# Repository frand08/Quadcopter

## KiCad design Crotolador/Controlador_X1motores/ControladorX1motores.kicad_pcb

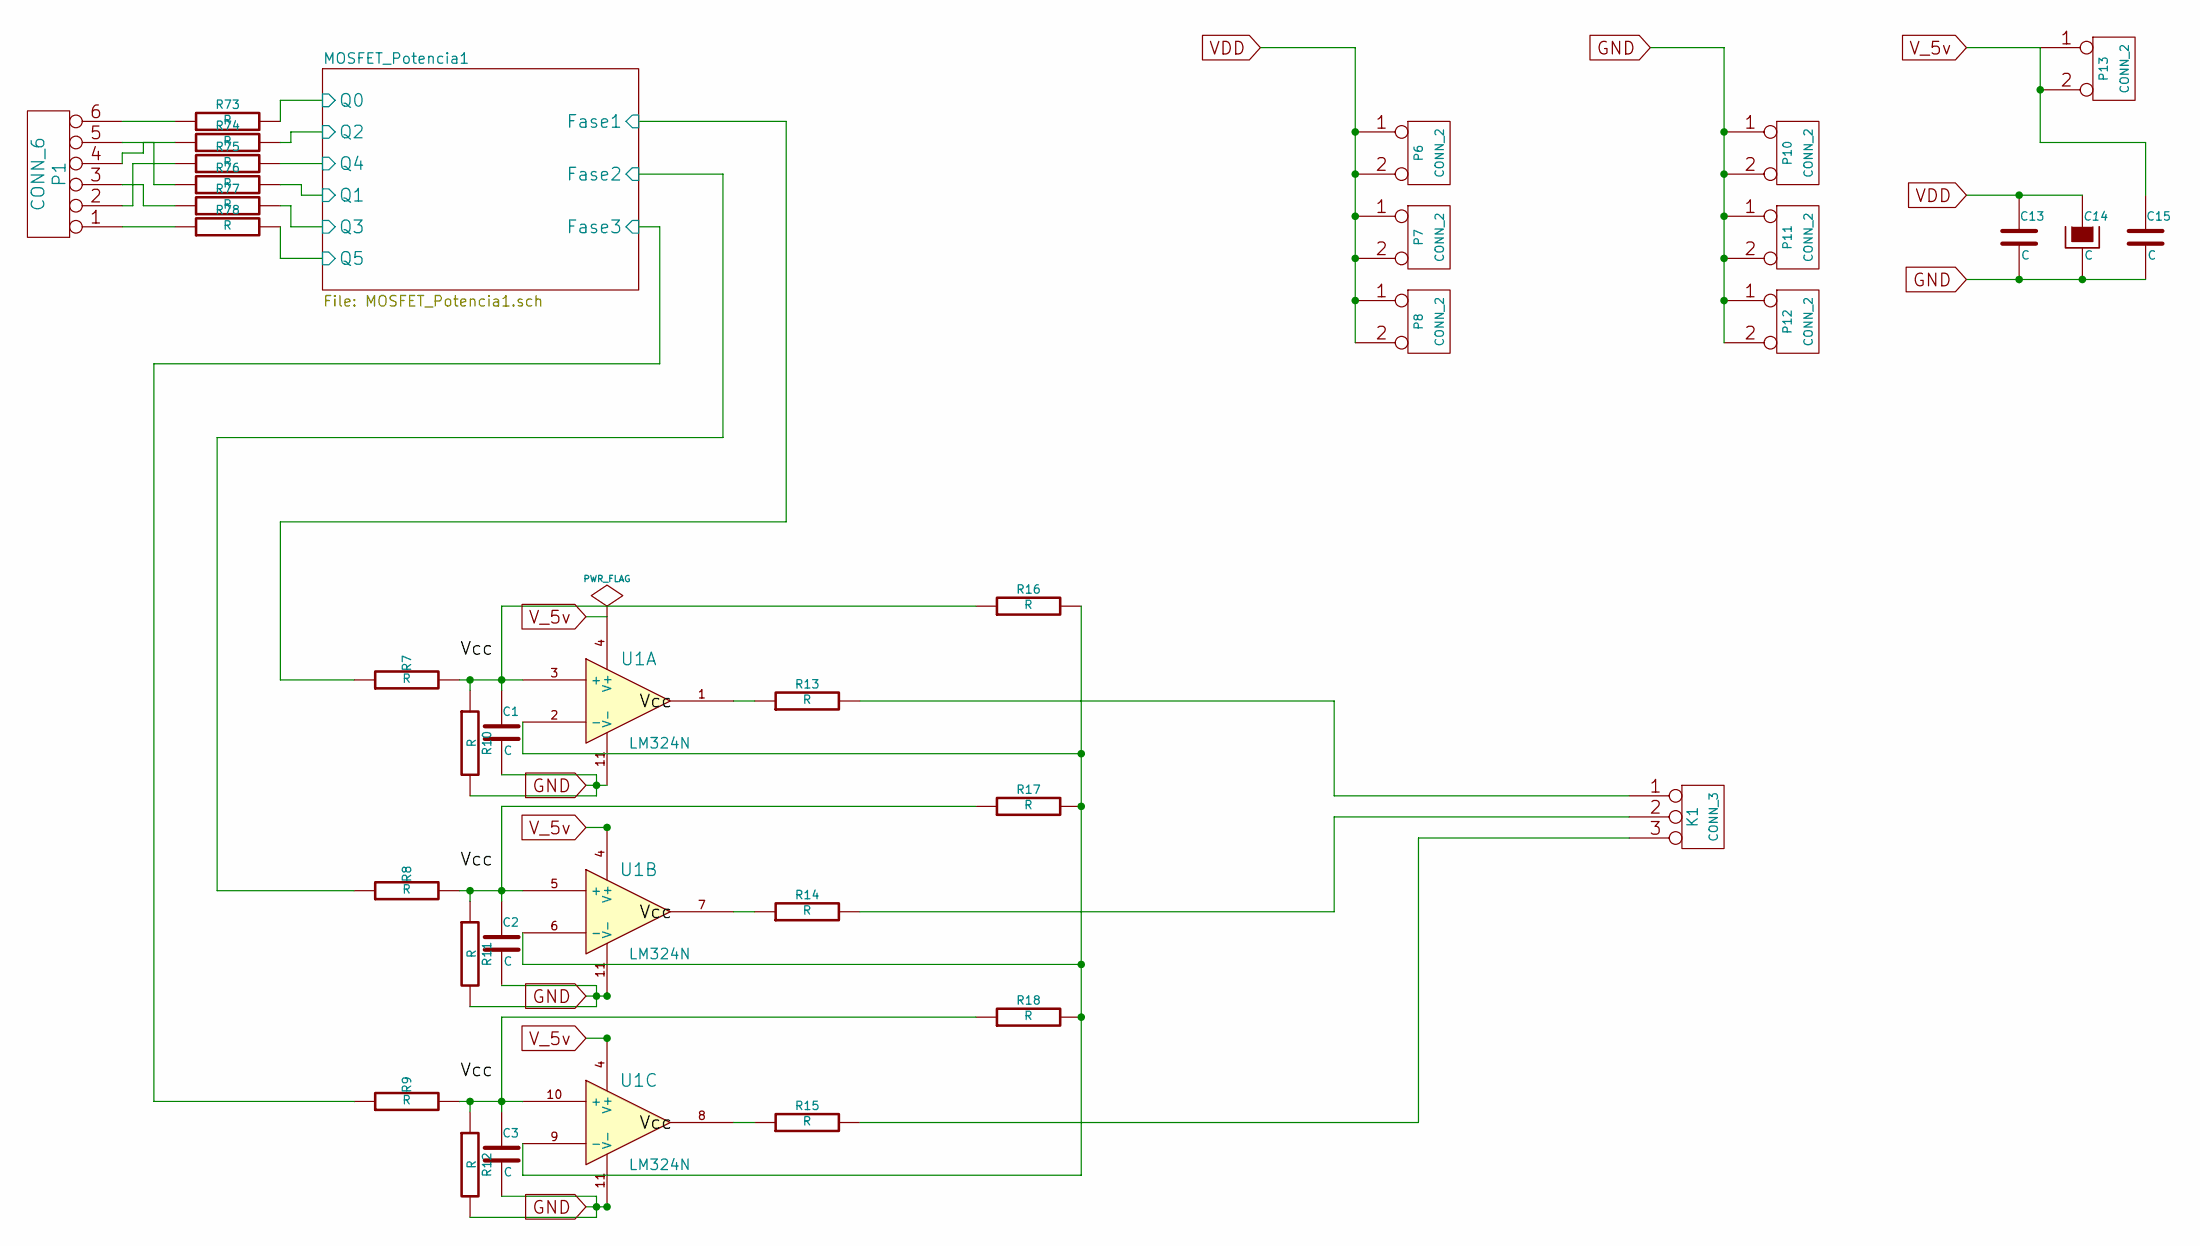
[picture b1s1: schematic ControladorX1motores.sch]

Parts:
C1, C2, C3, C13, C14, C15: C
K1: CONN_3
P1: CONN_6
P6, P7, P8, P10, P11, P12, P13: CONN_2
R7, R8, R9, R10, R11, R12, R13, R14, R15, R16, R17, R18, R73, R74, R75, R76, R77, R78: R
U1: LM324N

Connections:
/MOSFET_Potencia1/Fase1: R7.1; also elsewhere on the board
/MOSFET_Potencia1/Fase2: R8.1; also elsewhere on the board
/MOSFET_Potencia1/Fase3: R9.1; also elsewhere on the board
/MOSFET_Potencia1/Q0: R73.2; also elsewhere on the board
/MOSFET_Potencia1/Q1: R76.2; also elsewhere on the board
/MOSFET_Potencia1/Q2: R74.2; also elsewhere on the board
/MOSFET_Potencia1/Q3: R77.2; also elsewhere on the board
/MOSFET_Potencia1/Q4: R75.2; also elsewhere on the board
/MOSFET_Potencia1/Q5: R78.2; also elsewhere on the board
GND: C1.2, C2.2, C3.2, C13.2, C14.2, C15.2, P10.1, P10.2 (PM), P11.1, P11.2 (PM), P12.1, P12.2 (PM), R10.2, R11.2, R12.2, U1.11 (V-); also elsewhere on the board
unnamed: C1.1, R7.2, R10.1, R16.1, U1.3 (+)
unnamed: R13.1, U1.1
unnamed: C2.1, R8.2, R11.1, R17.1, U1.5 (+)
unnamed: R14.1, U1.7
unnamed: C3.1, R9.2, R12.1, R18.1, U1.10 (+)
unnamed: R15.1, U1.8
unnamed: P1.6, R73.1
unnamed: P1.1, R78.1
unnamed: P1.2, R75.1
unnamed: P1.3, R77.1
unnamed: P1.4, R74.1
unnamed: P1.5, R76.1
unnamed: K1.1, R13.2
unnamed: K1.2 (PM), R14.2
unnamed: K1.3, R15.2
unnamed: R16.2, R17.2, R18.2, U1.2 (-), U1.6 (-), U1.9 (-)
VDD: C13.1, C14.1, P6.1, P6.2 (PM), P7.1, P7.2 (PM), P8.1, P8.2 (PM); also elsewhere on the board
V_5v: C15.1, P13.1, P13.2 (PM), U1.4 (V+)

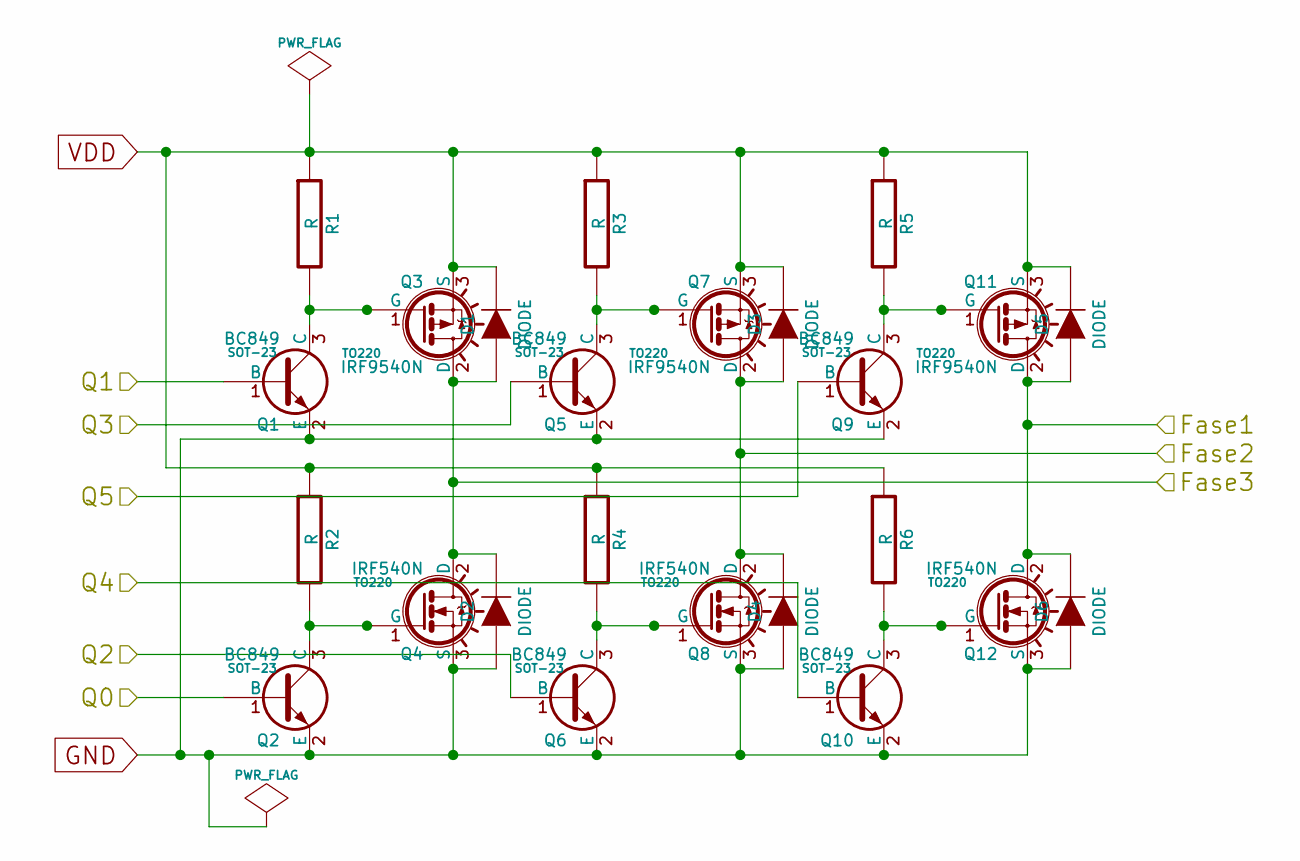
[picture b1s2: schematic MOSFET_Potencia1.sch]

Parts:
D1, D2, D3, D4, D5, D6: DIODE
Q1, Q2, Q5, Q6, Q9, Q10: BC849; SOT-23
Q3, Q7, Q11: IRF9540N; TO220
Q4, Q8, Q12: IRF540N; TO220
R1, R2, R3, R4, R5, R6: R

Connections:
/MOSFET_Potencia1/Fase1: D5.1 (A), D6.2 (K), Q11.2 (D), Q12.2 (D); also elsewhere on the board
/MOSFET_Potencia1/Fase2: D3.1 (A), D4.2 (K), Q7.2 (D), Q8.2 (D); also elsewhere on the board
/MOSFET_Potencia1/Fase3: D1.1 (A), D2.2 (K), Q3.2 (D), Q4.2 (D); also elsewhere on the board
/MOSFET_Potencia1/Q0: Q2.1 (B); also elsewhere on the board
/MOSFET_Potencia1/Q1: Q1.1 (B); also elsewhere on the board
/MOSFET_Potencia1/Q2: Q6.1 (B); also elsewhere on the board
/MOSFET_Potencia1/Q3: Q5.1 (B); also elsewhere on the board
/MOSFET_Potencia1/Q4: Q10.1 (B); also elsewhere on the board
/MOSFET_Potencia1/Q5: Q9.1 (B); also elsewhere on the board
GND: D2.1 (A), D4.1 (A), D6.1 (A), Q1.2 (E), Q2.2 (E), Q4.3 (S), Q5.2 (E), Q6.2 (E), Q8.3 (S), Q9.2 (E), Q10.2 (E), Q12.3 (S); also elsewhere on the board
unnamed: Q9.3 (C), Q11.1 (G), R5.2
unnamed: Q5.3 (C), Q7.1 (G), R3.2
unnamed: Q1.3 (C), Q3.1 (G), R1.2
unnamed: Q2.3 (C), Q4.1 (G), R2.2
unnamed: Q10.3 (C), Q12.1 (G), R6.2
unnamed: Q6.3 (C), Q8.1 (G), R4.2
VDD: D1.2 (K), D3.2 (K), D5.2 (K), Q3.3 (S), Q7.3 (S), Q11.3 (S), R1.1, R2.1, R3.1, R4.1, R5.1, R6.1; also elsewhere on the board

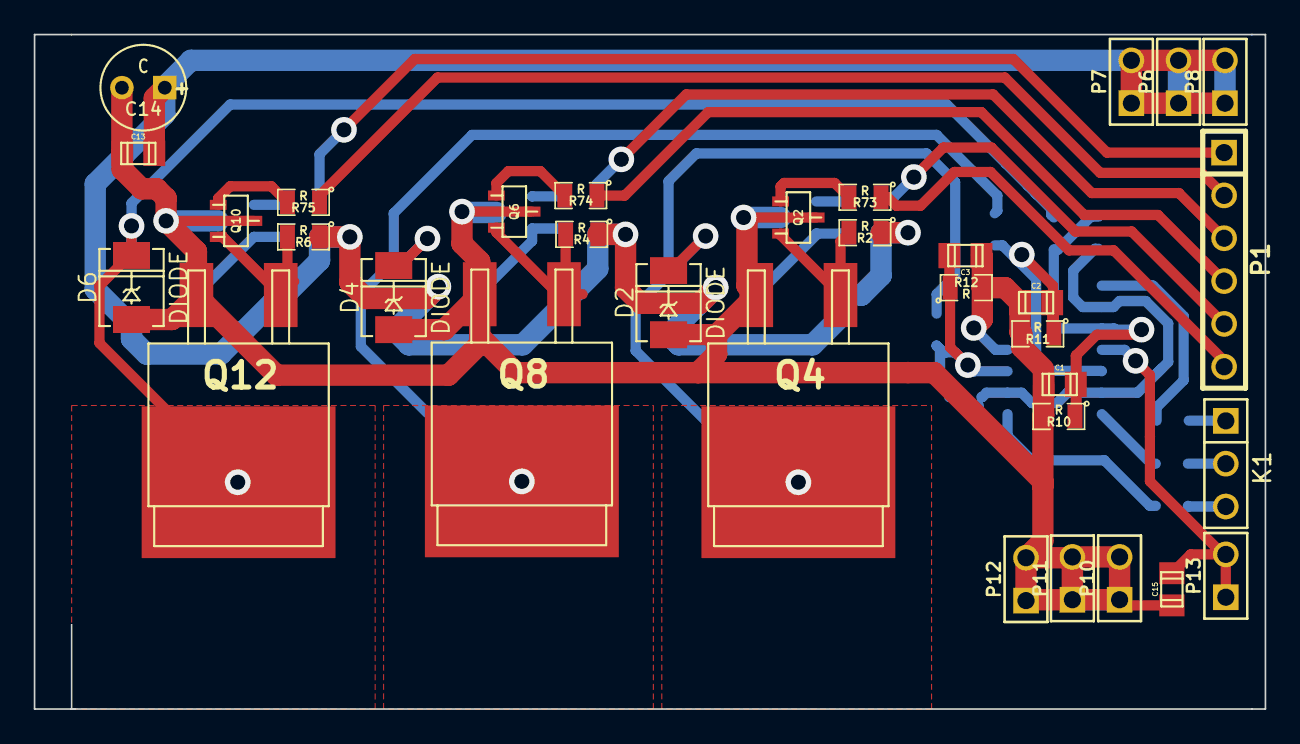
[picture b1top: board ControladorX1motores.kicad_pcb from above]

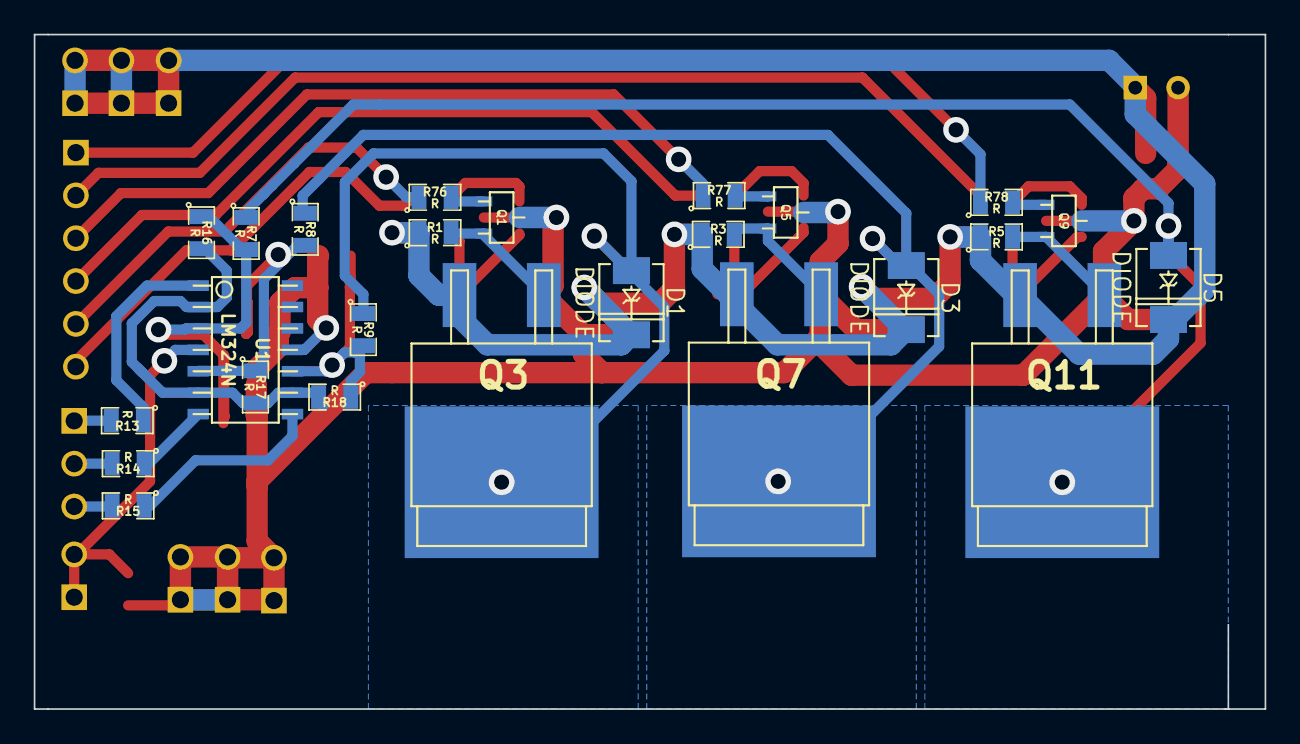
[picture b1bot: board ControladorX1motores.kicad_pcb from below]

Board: 2 copper layers, 73.0 x 40.0 mm, 58 parts (25 on the bottom side), 34 nets.

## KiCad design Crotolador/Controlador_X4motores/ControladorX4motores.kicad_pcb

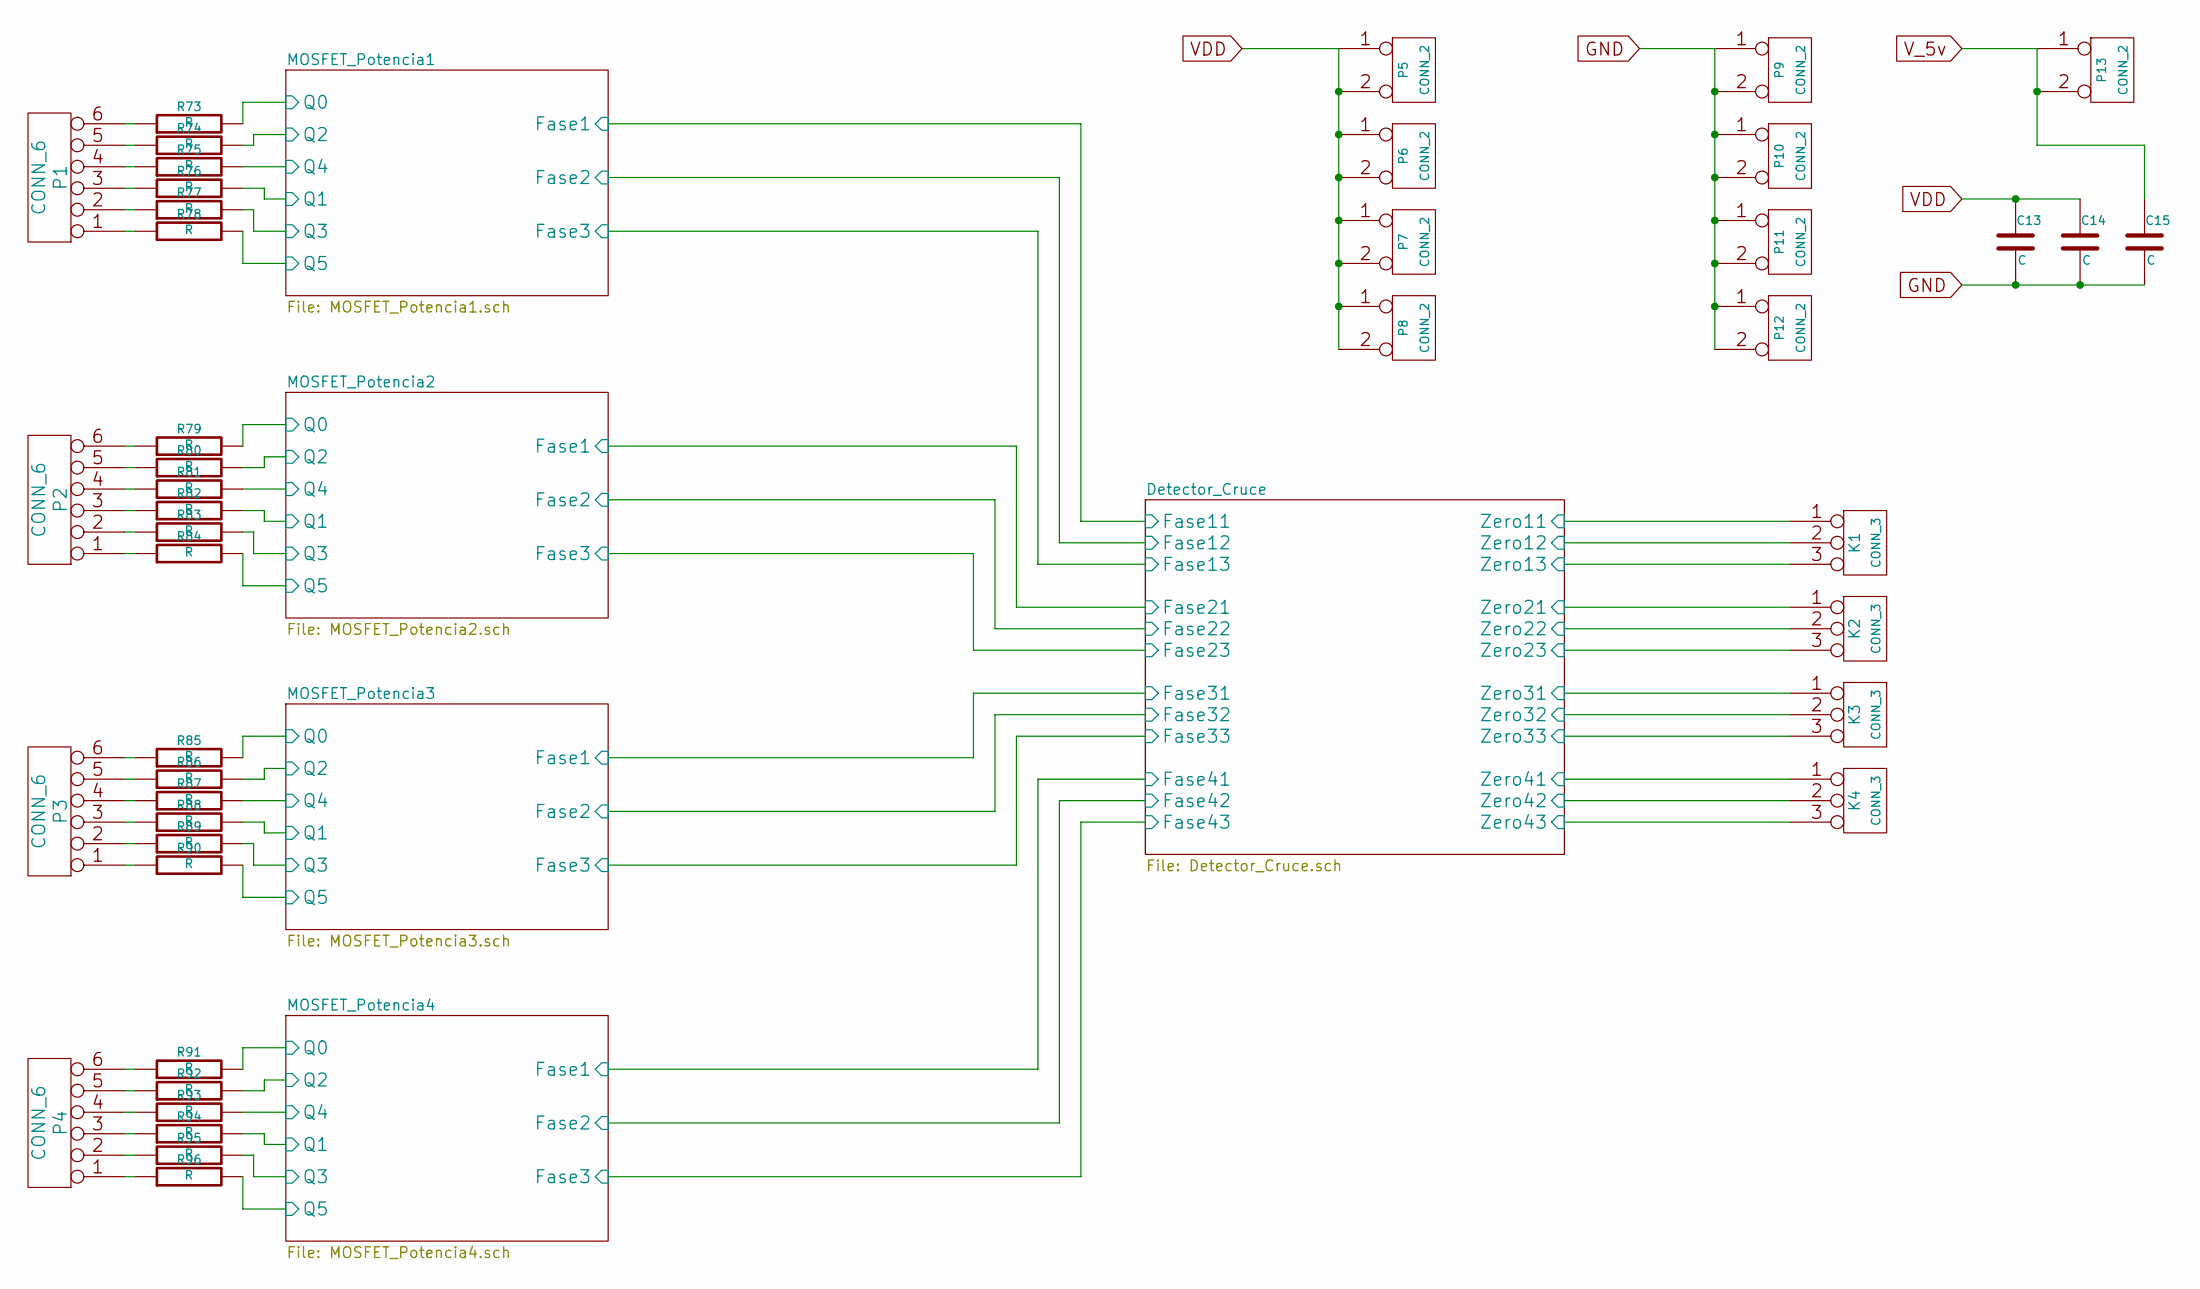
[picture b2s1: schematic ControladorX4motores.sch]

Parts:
C13, C14, C15: C
K1, K2, K3, K4: CONN_3
P1, P2, P3, P4: CONN_6
P5, P6, P7, P8, P9, P10, P11, P12, P13: CONN_2
R73, R74, R75, R76, R77, R78, R79, R80, R81, R82, R83, R84, R85, R86, R87, R88, R89, R90, R91, R92, R93, R94, R95, R96: R

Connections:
/Detector_Cruce/Zero11: K1.1; also elsewhere on the board
/Detector_Cruce/Zero12: K1.2 (PM); also elsewhere on the board
/Detector_Cruce/Zero13: K1.3; also elsewhere on the board
/Detector_Cruce/Zero21: K2.1; also elsewhere on the board
/Detector_Cruce/Zero22: K2.2 (PM); also elsewhere on the board
/Detector_Cruce/Zero23: K2.3; also elsewhere on the board
/Detector_Cruce/Zero31: K3.1; also elsewhere on the board
/Detector_Cruce/Zero32: K3.2 (PM); also elsewhere on the board
/Detector_Cruce/Zero33: K3.3; also elsewhere on the board
/Detector_Cruce/Zero41: K4.1; also elsewhere on the board
/Detector_Cruce/Zero42: K4.2 (PM); also elsewhere on the board
/Detector_Cruce/Zero43: K4.3; also elsewhere on the board
/MOSFET_Potencia1/Q0: R73.2; also elsewhere on the board
/MOSFET_Potencia1/Q1: R76.2; also elsewhere on the board
/MOSFET_Potencia1/Q2: R74.2; also elsewhere on the board
/MOSFET_Potencia1/Q3: R77.2; also elsewhere on the board
/MOSFET_Potencia1/Q4: R75.2; also elsewhere on the board
/MOSFET_Potencia1/Q5: R78.2; also elsewhere on the board
/MOSFET_Potencia2/Q0: R79.2; also elsewhere on the board
/MOSFET_Potencia2/Q1: R82.2; also elsewhere on the board
/MOSFET_Potencia2/Q2: R80.2; also elsewhere on the board
/MOSFET_Potencia2/Q3: R83.2; also elsewhere on the board
/MOSFET_Potencia2/Q4: R81.2; also elsewhere on the board
/MOSFET_Potencia2/Q5: R84.2; also elsewhere on the board
/MOSFET_Potencia3/Q0: R85.2; also elsewhere on the board
/MOSFET_Potencia3/Q1: R88.2; also elsewhere on the board
/MOSFET_Potencia3/Q2: R86.2; also elsewhere on the board
/MOSFET_Potencia3/Q3: R89.2; also elsewhere on the board
/MOSFET_Potencia3/Q4: R87.2; also elsewhere on the board
/MOSFET_Potencia3/Q5: R90.2; also elsewhere on the board
/MOSFET_Potencia4/Q0: R91.2; also elsewhere on the board
/MOSFET_Potencia4/Q1: R94.2; also elsewhere on the board
/MOSFET_Potencia4/Q2: R92.2; also elsewhere on the board
/MOSFET_Potencia4/Q3: R95.2; also elsewhere on the board
/MOSFET_Potencia4/Q4: R93.2; also elsewhere on the board
/MOSFET_Potencia4/Q5: R96.2; also elsewhere on the board
GND: C13.2, C14.2, C15.2, P9.1, P9.2 (PM), P10.1, P10.2 (PM), P11.1, P11.2 (PM), P12.1, P12.2 (PM); also elsewhere on the board
unnamed: P3.3, R88.1
unnamed: P3.4, R87.1
unnamed: P3.5, R86.1
unnamed: P3.6, R85.1
unnamed: P2.1, R84.1
unnamed: P3.2, R89.1
unnamed: P2.2, R83.1
unnamed: P2.3, R82.1
unnamed: P2.4, R81.1
unnamed: P2.5, R80.1
unnamed: P2.6, R79.1
unnamed: P4.3, R94.1
unnamed: P1.5, R74.1
unnamed: P1.6, R73.1
unnamed: P4.1, R96.1
unnamed: P4.2, R95.1
unnamed: P4.4, R93.1
unnamed: P4.5, R92.1
unnamed: P4.6, R91.1
unnamed: P3.1, R90.1
unnamed: P1.1, R78.1
unnamed: P1.2, R77.1
unnamed: P1.3, R76.1
unnamed: P1.4, R75.1
VDD: C13.1, C14.1, P5.1, P5.2 (PM), P6.1, P6.2 (PM), P7.1, P7.2 (PM), P8.1, P8.2 (PM); also elsewhere on the board
V_5v: C15.1, P13.1, P13.2 (PM); also elsewhere on the board

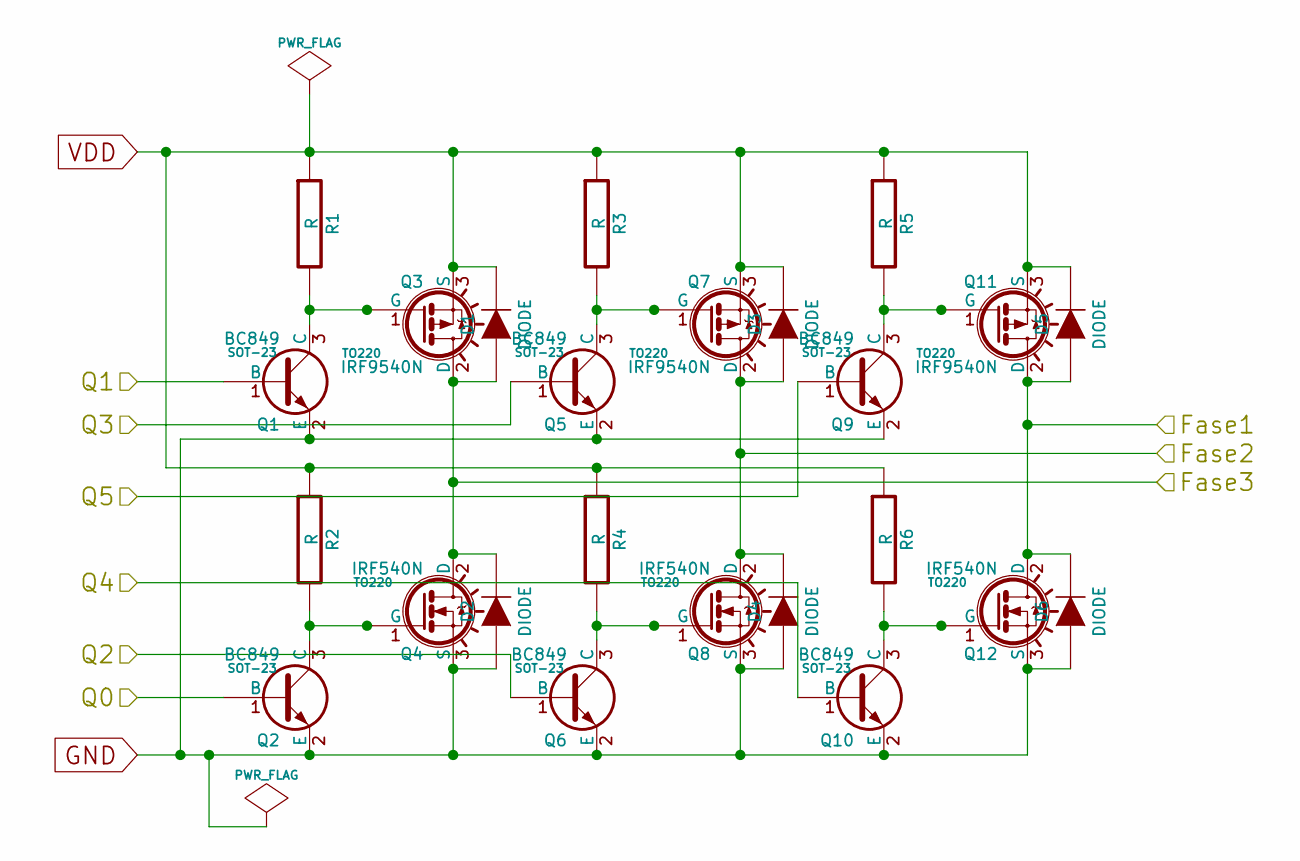
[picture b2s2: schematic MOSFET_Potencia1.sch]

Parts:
D1, D2, D3, D4, D5, D6: DIODE
Q1, Q2, Q5, Q6, Q9, Q10: BC849; SOT-23
Q3, Q7, Q11: IRF9540N; TO220
Q4, Q8, Q12: IRF540N; TO220
R1, R2, R3, R4, R5, R6: R

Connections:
/Detector_Cruce/Fase12: D3.1 (A), D4.2 (K), Q7.2 (D), Q8.2 (D); also elsewhere on the board
/Detector_Cruce/Fase13: D1.1 (A), D2.2 (K), Q3.2 (D), Q4.2 (D); also elsewhere on the board
/MOSFET_Potencia1/Fase1: D5.1 (A), D6.2 (K), Q11.2 (D), Q12.2 (D); also elsewhere on the board
/MOSFET_Potencia1/Q0: Q2.1 (B); also elsewhere on the board
/MOSFET_Potencia1/Q1: Q1.1 (B); also elsewhere on the board
/MOSFET_Potencia1/Q2: Q6.1 (B); also elsewhere on the board
/MOSFET_Potencia1/Q3: Q5.1 (B); also elsewhere on the board
/MOSFET_Potencia1/Q4: Q10.1 (B); also elsewhere on the board
/MOSFET_Potencia1/Q5: Q9.1 (B); also elsewhere on the board
GND: D2.1 (A), D4.1 (A), D6.1 (A), Q1.2 (E), Q2.2 (E), Q4.3 (S), Q5.2 (E), Q6.2 (E), Q8.3 (S), Q9.2 (E), Q10.2 (E), Q12.3 (S); also elsewhere on the board
unnamed: Q5.3 (C), Q7.1 (G), R3.2
unnamed: Q1.3 (C), Q3.1 (G), R1.2
unnamed: Q9.3 (C), Q11.1 (G), R5.2
unnamed: Q6.3 (C), Q8.1 (G), R4.2
unnamed: Q2.3 (C), Q4.1 (G), R2.2
unnamed: Q10.3 (C), Q12.1 (G), R6.2
VDD: D1.2 (K), D3.2 (K), D5.2 (K), Q3.3 (S), Q7.3 (S), Q11.3 (S), R1.1, R2.1, R3.1, R4.1, R5.1, R6.1; also elsewhere on the board

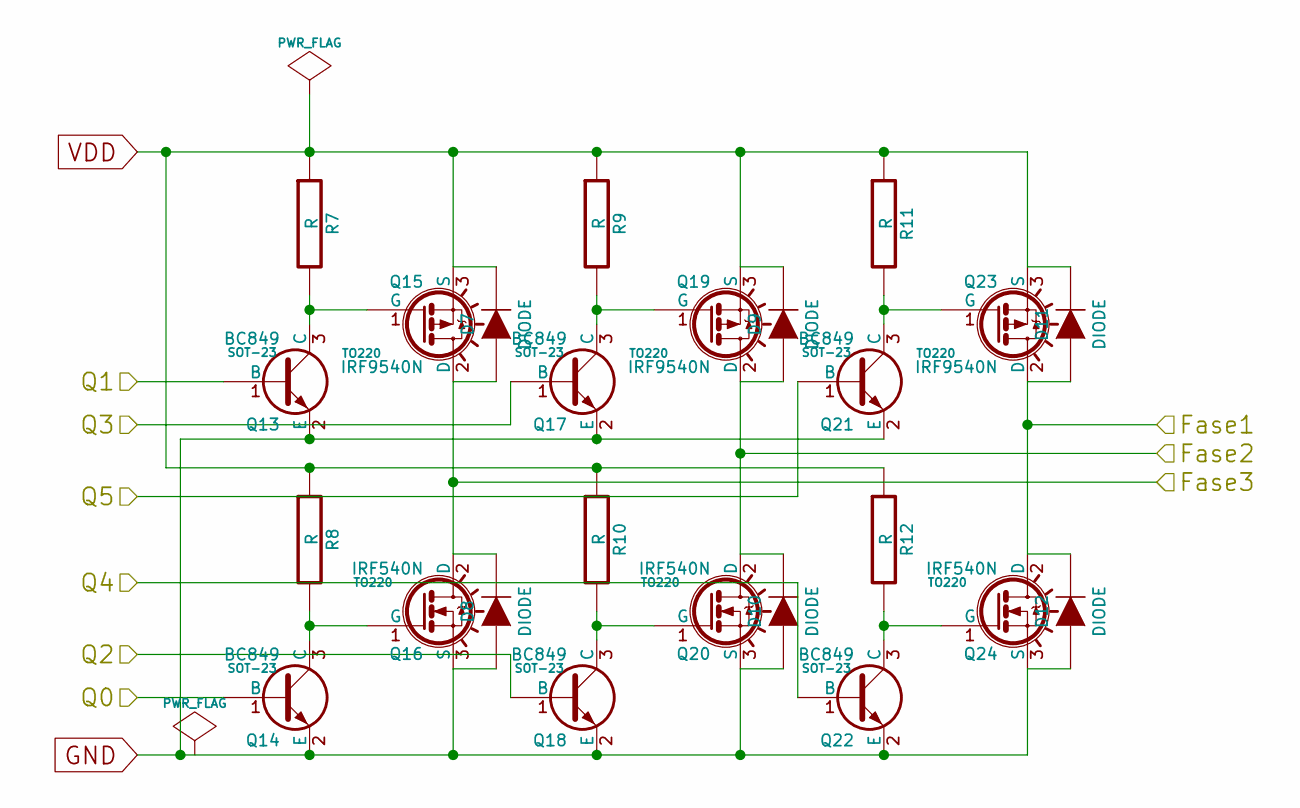
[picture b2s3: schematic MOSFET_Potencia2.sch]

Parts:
D7, D8, D9, D10, D11, D12: DIODE
Q13, Q14, Q17, Q18, Q21, Q22: BC849; SOT-23
Q15, Q19, Q23: IRF9540N; TO220
Q16, Q20, Q24: IRF540N; TO220
R7, R8, R9, R10, R11, R12: R

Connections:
/Detector_Cruce/Fase23: D7.1 (A), D8.2 (K), Q15.2 (D), Q16.2 (D); also elsewhere on the board
/MOSFET_Potencia2/Fase1: D11.1 (A), D12.2 (K), Q23.2 (D), Q24.2 (D); also elsewhere on the board
/MOSFET_Potencia2/Fase2: D9.1 (A), D10.2 (K), Q19.2 (D), Q20.2 (D); also elsewhere on the board
/MOSFET_Potencia2/Q0: Q14.1 (B); also elsewhere on the board
/MOSFET_Potencia2/Q1: Q13.1 (B); also elsewhere on the board
/MOSFET_Potencia2/Q2: Q18.1 (B); also elsewhere on the board
/MOSFET_Potencia2/Q3: Q17.1 (B); also elsewhere on the board
/MOSFET_Potencia2/Q4: Q22.1 (B); also elsewhere on the board
/MOSFET_Potencia2/Q5: Q21.1 (B); also elsewhere on the board
GND: D8.1 (A), D10.1 (A), D12.1 (A), Q13.2 (E), Q14.2 (E), Q16.3 (S), Q17.2 (E), Q18.2 (E), Q20.3 (S), Q21.2 (E), Q22.2 (E), Q24.3 (S); also elsewhere on the board
unnamed: Q18.3 (C), Q20.1 (G), R10.2
unnamed: Q13.3 (C), Q15.1 (G), R7.2
unnamed: Q17.3 (C), Q19.1 (G), R9.2
unnamed: Q22.3 (C), Q24.1 (G), R12.2
unnamed: Q21.3 (C), Q23.1 (G), R11.2
unnamed: Q14.3 (C), Q16.1 (G), R8.2
VDD: D7.2 (K), D9.2 (K), D11.2 (K), Q15.3 (S), Q19.3 (S), Q23.3 (S), R7.1, R8.1, R9.1, R10.1, R11.1, R12.1; also elsewhere on the board

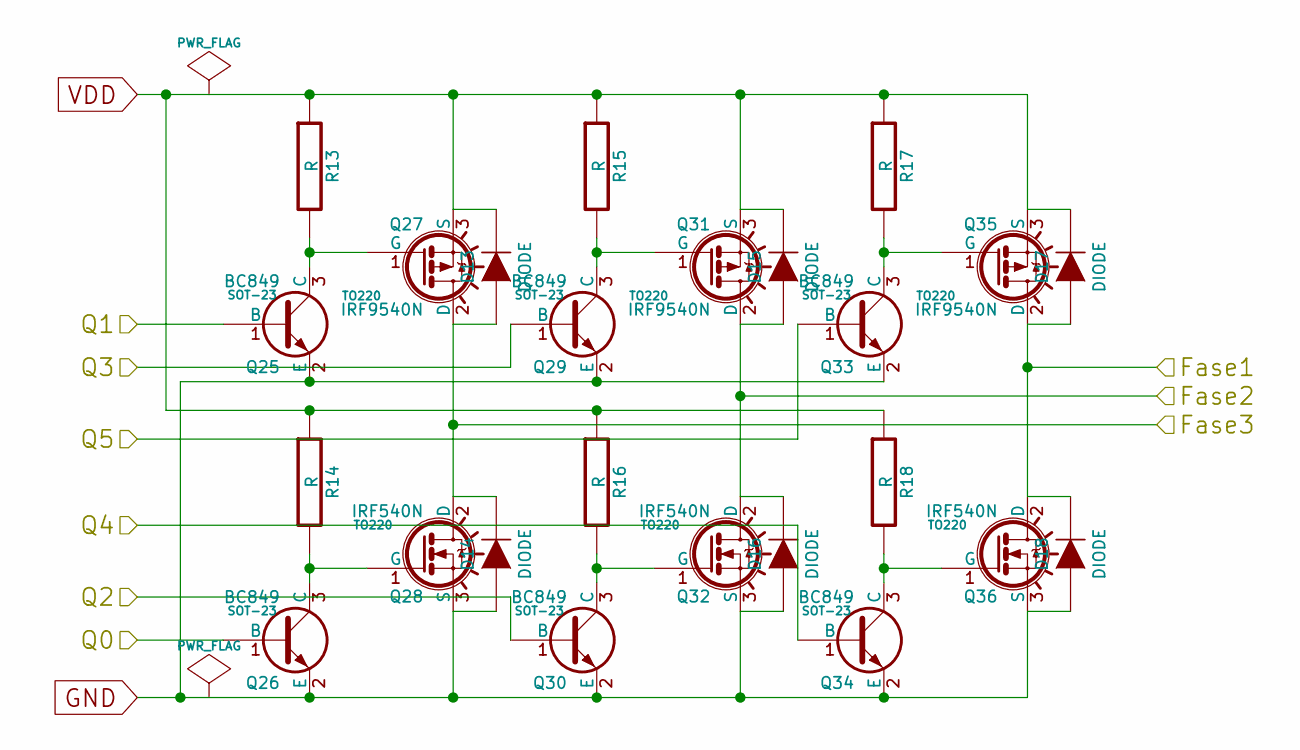
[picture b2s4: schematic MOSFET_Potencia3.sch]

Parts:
D13, D14, D15, D16, D17, D18: DIODE
Q25, Q26, Q29, Q30, Q33, Q34: BC849; SOT-23
Q27, Q31, Q35: IRF9540N; TO220
Q28, Q32, Q36: IRF540N; TO220
R13, R14, R15, R16, R17, R18: R

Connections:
/MOSFET_Potencia3/Fase1: D17.1 (A), D18.2 (K), Q35.2 (D), Q36.2 (D); also elsewhere on the board
/MOSFET_Potencia3/Fase2: D15.1 (A), D16.2 (K), Q31.2 (D), Q32.2 (D); also elsewhere on the board
/MOSFET_Potencia3/Fase3: D13.1 (A), D14.2 (K), Q27.2 (D), Q28.2 (D); also elsewhere on the board
/MOSFET_Potencia3/Q0: Q26.1 (B); also elsewhere on the board
/MOSFET_Potencia3/Q1: Q25.1 (B); also elsewhere on the board
/MOSFET_Potencia3/Q2: Q30.1 (B); also elsewhere on the board
/MOSFET_Potencia3/Q3: Q29.1 (B); also elsewhere on the board
/MOSFET_Potencia3/Q4: Q34.1 (B); also elsewhere on the board
/MOSFET_Potencia3/Q5: Q33.1 (B); also elsewhere on the board
GND: D14.1 (A), D16.1 (A), D18.1 (A), Q25.2 (E), Q26.2 (E), Q28.3 (S), Q29.2 (E), Q30.2 (E), Q32.3 (S), Q33.2 (E), Q34.2 (E), Q36.3 (S); also elsewhere on the board
unnamed: Q33.3 (C), Q35.1 (G), R17.2
unnamed: Q29.3 (C), Q31.1 (G), R15.2
unnamed: Q34.3 (C), Q36.1 (G), R18.2
unnamed: Q30.3 (C), Q32.1 (G), R16.2
unnamed: Q26.3 (C), Q28.1 (G), R14.2
unnamed: Q25.3 (C), Q27.1 (G), R13.2
VDD: D13.2 (K), D15.2 (K), D17.2 (K), Q27.3 (S), Q31.3 (S), Q35.3 (S), R13.1, R14.1, R15.1, R16.1, R17.1, R18.1; also elsewhere on the board

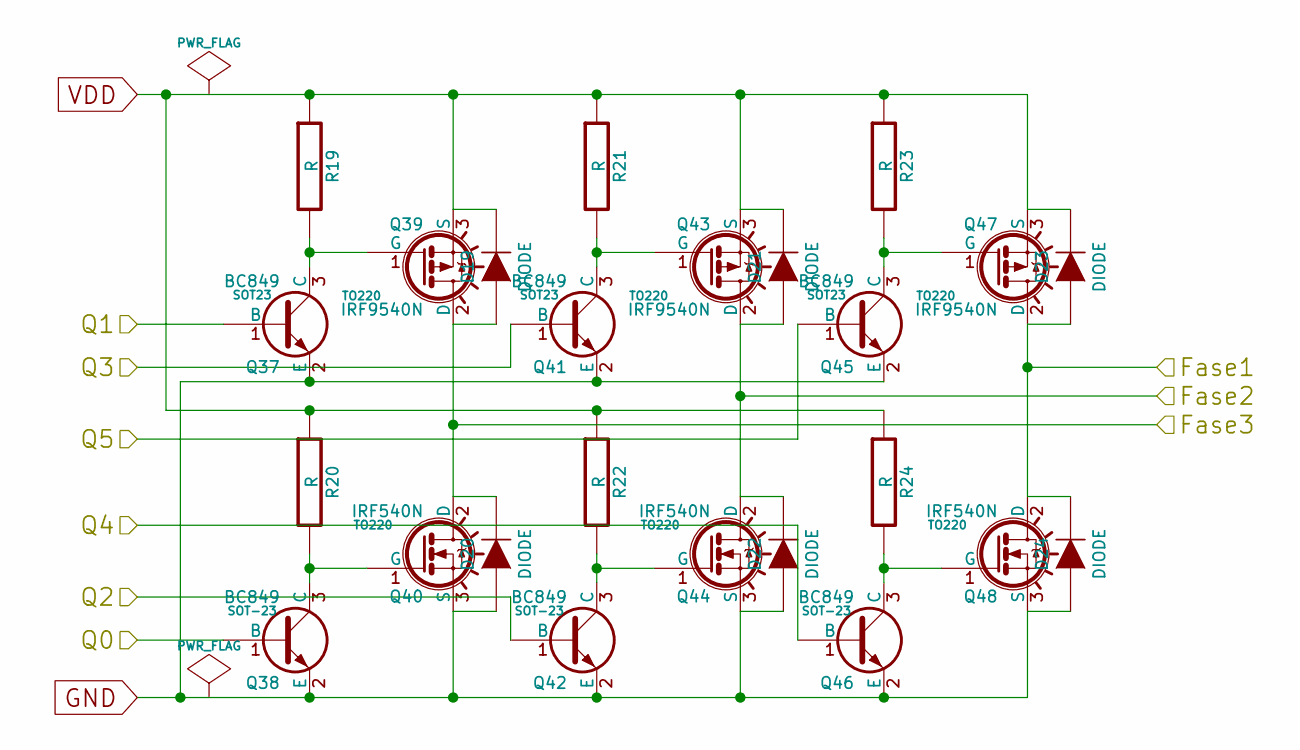
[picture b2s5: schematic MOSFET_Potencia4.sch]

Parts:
D19, D20, D21, D22, D23, D24: DIODE
Q37, Q41, Q45: BC849; SOT23
Q38, Q42, Q46: BC849; SOT-23
Q39, Q43, Q47: IRF9540N; TO220
Q40, Q44, Q48: IRF540N; TO220
R19, R20, R21, R22, R23, R24: R

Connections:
/MOSFET_Potencia4/Fase1: D23.1 (A), D24.2 (K), Q47.2 (D), Q48.2 (D); also elsewhere on the board
/MOSFET_Potencia4/Fase2: D21.1 (A), D22.2 (K), Q43.2 (D), Q44.2 (D); also elsewhere on the board
/MOSFET_Potencia4/Fase3: D19.1 (A), D20.2 (K), Q39.2 (D), Q40.2 (D); also elsewhere on the board
/MOSFET_Potencia4/Q0: Q38.1 (B); also elsewhere on the board
/MOSFET_Potencia4/Q1: Q37.1 (B); also elsewhere on the board
/MOSFET_Potencia4/Q2: Q42.1 (B); also elsewhere on the board
/MOSFET_Potencia4/Q3: Q41.1 (B); also elsewhere on the board
/MOSFET_Potencia4/Q4: Q46.1 (B); also elsewhere on the board
/MOSFET_Potencia4/Q5: Q45.1 (B); also elsewhere on the board
GND: D20.1 (A), D22.1 (A), D24.1 (A), Q37.2 (E), Q38.2 (E), Q40.3 (S), Q41.2 (E), Q42.2 (E), Q44.3 (S), Q45.2 (E), Q46.2 (E), Q48.3 (S); also elsewhere on the board
unnamed: Q37.3 (C), Q39.1 (G), R19.2
unnamed: Q41.3 (C), Q43.1 (G), R21.2
unnamed: Q38.3 (C), Q40.1 (G), R20.2
unnamed: Q46.3 (C), Q48.1 (G), R24.2
unnamed: Q45.3 (C), Q47.1 (G), R23.2
unnamed: Q42.3 (C), Q44.1 (G), R22.2
VDD: D19.2 (K), D21.2 (K), D23.2 (K), Q39.3 (S), Q43.3 (S), Q47.3 (S), R19.1, R20.1, R21.1, R22.1, R23.1, R24.1; also elsewhere on the board
